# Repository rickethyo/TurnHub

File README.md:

# TurnHub

TurnHub is a local-first tabletop game-management system: turn timer, lobby,
life totals and Commander damage, player profiles and statistics. An
authoritative **Atlas** table controller runs connected games; player-facing
**Sigils**, phones and tablets and the Atlas touchscreen request the same
semantic actions from it. The Android app also runs separate standalone games;
an iPhone/iPad app is at the framework stage.

**Current firmware:** Atlas **0.7.17-dev**, Sigil **0.9.19-dev** (protocol 3).
Signed releases are published on GitHub Releases and installed from the
Android app or the Atlas portal.

Earlier Python/Raspberry Pi generations are recorded in
[Generation History](Documentation/engineering/history/GENERATION_HISTORY.md). They are
not part of this repository or the current runtime.

## Branches

`master` is the ESP32-S3/LVGL development track. The current ESP32 boards
(e-ink and OLED Sigils, the 2.8" Atlas), the test harness, the Sigil v1 PCB and
the 3D enclosures are frozen on **`legacy/gen1`**: to fix a bug on those boards,
branch from `legacy/gen1` and open the PR against it. The two never merge.

## Where to look

| Path | What |
|---|---|
| [`Atlas/`](Atlas/README.md) | ESP32 table controller: game engine, Wi-Fi AP, web portal and HTTP API, ESP-NOW radio, NVS and optional microSD storage |
| [`Sigil/`](Sigil/platformio.ini) | Touchscreen player controller: LVGL touch buttons, secure radio, pairing and speaker; one build, on the E32R28T board until the S3 Sigil |
| [`shared/simulator/`](shared/simulator/README.md) | Semi-retired desktop simulator; real Atlas/Sigil hardware is primary |
| [`Android/`](Android/README.md) | Native client: table view, player controls, guided setup and firmware updates |
| [`iOS/`](iOS/README.md) | SwiftUI iPhone/iPad foundation, core package and staged development plan; gameplay not yet implemented |
| [`protocol/`](protocol/README.md) | Client contract: JSON schemas, [`http-v1.md`](protocol/http-v1.md), example responses |
| [`shared/display/`](shared/display) | Active fonts and icons shared by Atlas, Sigil and optional simulator |
| [`shared/include/`](shared/include) | Firmware headers shared by Atlas and Sigil (radio contract, firmware package format) |
| [`Documentation/engineering/`](Documentation/engineering/README.md) | The engineering record: invariants, design references, staged work |
| [`Documentation/User Manual/`](Documentation/User%20Manual) | The user manuals: the App Manual and the Hardware Manual (newest `.docx` of each; the app bundles both) |

## Core architectural rule

**Atlas owns canonical game and table state.** Sigils, phones, the Atlas
touchscreen and simulators submit Intents and render Atlas state.
They never advance turns, resolve wins, own player identity or keep competing
game engines. See [Architectural Invariants](Documentation/engineering/ARCHITECTURAL_INVARIANTS.md).

```text
Profile (optional persistent person)
  -> Participant (one person at the current table)
    -> Controller assignment(s): physical Sigil seat, browser sessions, the app
```

Changing controllers never replaces the participant or moves its statistics.

## What works today

- Lobby with any-seated-player start (cancellable countdown), starter choice,
  turn passing with a three-second cancellable grace, pause/resume, concession,
  elimination, win claim/confirm, draw by the Atlas End match hold, rematch and reset.
- Game profiles (Generic, Magic, Commander, Yu-Gi-Oh!) with life totals,
  Commander damage and cross-player life requests the recipient approves.
- Turn timer with warning and expiry cues on Sigil lights and buzzers, the
  Atlas speaker and phones, with per-player accessibility preferences.
- Local profiles with PINs, phone-only and mixed phone/Sigil play, a Sigil
  profile picker, Admin/Game Master/Developer permissions, and table presence
  codes for protected actions.
- Deliberate pairing (60 s minimum window) over an encrypted Atlas-Sigil link,
  with forget/unpair and factory reset from menus, the portal and the BOOT button.
- Interrupted-match recovery: a power cut restores the match paused.
- Core statistics in NVS; detailed statistics, avatars and rotating
  diagnostics on an optional microSD card.
- Signed firmware updates for Atlas and both Sigil variants, delivered from
  the Android app or the portal, plus a first-run guided setup in the app.

Known limits are tracked in [Staged Changes](Documentation/engineering/STAGED_CHANGES.md).
The most important: statistics are not yet crash-safe exactly-once
([completion ordering](Documentation/engineering/STORAGE_AND_RECOVERY.md)).

## Persistence

Survives restart: profiles, PIN hashes, permissions and policy, core
statistics, seat bindings, pairings, game settings, accessibility
preferences, the Wi-Fi password, speaker volume, setup stage and touch
calibration (NVS); detailed statistics and diagnostics (microSD, optional).

RAM only: browser sessions, lobby participation and live game state, except
the interrupted-match recovery record, which restores paused and never
replays statistics.

## Building and testing

Commands for every target are in [`CLAUDE.md`](CLAUDE.md) and each
directory's README. CI (`.github/workflows/ci.yml`) runs the host suites,
contract checks, supported firmware builds and the Android tests; see
[Continuous Integration](Documentation/engineering/CONTINUOUS_INTEGRATION.md).

## Local-first

The core play path never needs a cloud service, subscription or internet
connection. Atlas serves the table on its own Wi-Fi. The broader ownership,
repairability, privacy and accessibility direction is in
[Product Principles](Documentation/PRODUCT_PRINCIPLES.md).

## Status

TurnHub is a prototype. Every Atlas and Sigil is reflashed together,
so there is no backward compatibility before release: a changed protocol or
storage layout means reflashing everything and, for storage, a factory reset.

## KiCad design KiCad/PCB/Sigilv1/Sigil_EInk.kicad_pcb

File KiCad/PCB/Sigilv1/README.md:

# Sigil Rev A electrical drafts

Rev A is drawn as two KiCad projects in this folder, plus `Sigil_JewelAdapter` (the status ring's small board, below). They share the symbol library (`Sigil.kicad_sym`) and differ only in the display interface:

| Project | Display | Display nets |
|---|---|---|
| `Sigil_EInk.kicad_pro` | Inland e-paper driver board (GxEPD2_213_B74), J2 `EPD_Module_Header` (8 pins) | EPD_SCLK, EPD_MOSI, EPD_CS, EPD_DC, EPD_RST, EPD_BUSY |
| `Sigil_OLED.kicad_pro` | Inland 1.3" OLED V2.0, J2 `OLED_Module_Header` (7 pins) | OLED_SCLK, OLED_MOSI, OLED_CS, OLED_DC, OLED_RST |

Both displays use the same sockets and GPIOs (A8/GPIO16 DC, A9/GPIO17 CS, A11/GPIO18 clock, A17/GPIO22 reset, A18/GPIO23 data); only the e-ink uses A14/GPIO21 BUSY. Both schematics also carry the buzzer interface J3 on J12/GPIO33, +3V3 from J19, and GND on A13, A19 and J6.

**Discrete LEDs and the old buttons are gone** (removed 2026-09-24). Their GPIOs are marked NC.

**Display-type strap (both, 2026-09-26).** A7/GPIO4 tells the firmware which display the board carries (`HW_TYPE_STRAP_PIN`, `Sigil/DISPLAY.md`): left NC on `Sigil_EInk` (the internal pull-up reads E-ink), tied to GND on `Sigil_OLED`. A build for the other display halts at boot, so a carrier with the wrong strap won't run.

**First-PCB footprints (2026-09-26).** Every carrier part now has a footprint and is in the BOM (through-hole except U2, SOT-23-5; U1 and the Jewel pins are local footprints in `Sigil.pretty`): J2 a 1x8 (E-ink) or 1x7 (OLED) 2.54 mm socket, J4 a JST-XH 5-pin socket for the joystick harness, J5 a JST-XH 3-pin socket for the Jewel adapter pigtail, J3 a 1x2 header for the buzzer leads, R1 an axial 0207 resistor, C2 a 10 uF ceramic on +3V3 beside the headers (5 mm disc footprint). *Planned*: footprints are chosen, no board is laid out.

**Joystick (both).** Both schematics carry J4, an unmarked 5-pin analog thumbstick that replaces the Pass/Action/Pause buttons: GND, "+5V" (fed **3.3 V**, never 5 V, since VRX/VRY swing to the supply and the ESP32 ADC is 3.3 V max), VRX to J15/GPIO34, VRY to J14/GPIO35 and SW to J13/GPIO32. VRX/VRY are ADC1 input-only pins because ADC2 is unusable under ESP-NOW. Firmware: the Sigil `sigil` and `sigil-oled` PlatformIO environments; the directions and click are the five menu keys. *Verified* on the owner's E-ink breadboard (2026-09-25): both axes read reversed as mounted, so the firmware inverts X and Y. The OLED Sigil's five pushbuttons (SW1-SW5) were replaced by the same stick on the same GPIOs on 2026-10-01 (owner); its mounting *Needs verification*.

**Status ring (both), on its own adapter board (2026-09-26).** The Adafruit NeoPixel Jewel 7 (RGBW) no longer sits on the Sigil board. `Sigil_JewelAdapter` is a small board with five pin holes where the Jewel's pads are (positions from Adafruit's [NeoJewel 7 board file](https://github.com/adafruit/Adafruit-NeoPixel-Jewel-7)): pins stand up from it and the Jewel is soldered on top, LEDs up, like it was on the breadboard. It carries C1 (470 uF bulk capacitor), the Jewel's two M2 mounting holes, an optional unfitted chain-out J3 (+5V, DOUT, GND) for more pixels after the Jewel, and J2, three holes for the bare end of a 3-wire JST-XH pigtail. The pigtail plugs into J5 on the Sigil board, a JST-XH 3-pin socket (1 +5V, 2 DIN, 3 GND, same order at both ends). On the Sigil board, GPIO26 (J10) goes through U2 and R1 (330 ohm, at the source; the Jewel has its own 470 ohm on DIN) to J5, and +5V comes from the DevKit's USB 5V (J1). Full RGBW draws about 560 mA, more than USB supplies, so the firmware caps brightness at 48/255. The ring draws the Sigil's status light from Atlas's LedState; the same information is always on a screen as text. *Verified* lit on the breadboard (owner, 2026-09-26); the adapter's pad positions are *Needs verification* (test-fit a Jewel against a 1:1 print).

**Front light output J6 (both, 2026-09-28).** A second JST-XH 3-pin socket for the possible player-facing strip on the case front lip (`STAGED_CHANGES.md`). It has its own data line rather than chaining off the Jewel adapter: the main board sits in the case base beside the front lip, while the Jewel is on the back wall. GPIO13 (socket J5; free on both boards and not a boot strap) goes through U3 (a second 74AHCT1G125, decoupled by C4) and R2 (330 ohm) to J6 pin 2; pinout as J5 (1 +5V, 2 DIN, 3 GND). J6, U3, R2 and C4 are fitted on every board (owner decision) so a strip can be added later without rework. Ring and strip share USB 5 V, so firmware must cap both (7 + 8 RGBW pixels at 48/255 is about 225 mA). No firmware drives GPIO13 yet. *Planned*.

The breadboard wiring the current firmware uses is in the [hardware reference](../../../Documentation/engineering/HARDWARE.md).

U1 is the removable, complete 38-pin ESP32 DevKit carrier interface (Inland ESP32-WROOM-32E, micro-USB, the narrow 38-pin format). Its custom symbol and local symbol library use **A1–A19 and J1–J19 as pin numbers**, not ESP32 module pad numbers. Its footprint, `Sigil.pretty/ESP32_DevKit_38_Socket_Row22.225mm` (from `build_schematic.py`), has 2.54 mm pitch and rows 22.225 mm (7/8 in) apart, and a 25.4 x 53.975 mm (1 x 2 1/8 in) outline that is not centred on the pins: the owner's breadboard fit (2026-09-28, first pins in row 1, USB end flush with the breadboard end, antenna end just reaching row 21) puts the USB end about 3.4 mm before A1/J1 and the antenna end about 4.86 mm past A19/J19. Row spacing, width, length and antenna size are the owner's ruler measurements (2026-09-28; 7/8 in rows, 1 in wide, antenna 1/4 in long from 1 7/8 in). An earlier breadboard fit suggested 22.86 mm (0.9 in), which conflicts by 0.635 mm. A 6.35 mm keep-out (no tracks, vias, pours or parts), 3/4 in wide so the pin rows stay routable, covers the WROOM-32E antenna at the A19/J19 end. It is drawn from the carrier's top side with the DevKit face up and micro-USB at the top, which mirrors the rear photo: the A row is on the left, the J row on the right, and A1/J1 at the USB end. *Needs verification*: caliper-check the row spacing and test-fit sockets before ordering. `Sigil_EInk.kicad_pcb` is routed (2026-09-28, Freerouting v2.4.1 plus a hand-placed BUZZER track, GND pours on both layers with solid pad connections); KiCad 10.0.6 CLI DRC reports 0 violations, 0 unconnected pads and 0 schematic parity issues. It is not fabrication-ready until U1 is test-fitted. The OLED PCB is still an empty placeholder.

## Authority and orientation

- GPIO functions: `Sigil/include/epaper_display.h` and the explicit SPI configuration in `Sigil/src/epaper_display.cpp` (e-ink), `Sigil/include/oled_config.h` (OLED), and `BUZZER_PIN` in `Sigil/src/main.cpp`.
- Socket identity: user-supplied [SigilBackMarked.png](reference/SigilBackMarked.png), photographed from the **BACK**, and the user's transcribed sequence. The schematics deliberately show J1 (5V) top-left and A1 (CLK) top-right in that rear-reference view.
- [The cross-check tables](CROSS_CHECK.md) are verified from both exported netlists and the firmware by `tools/verify_schematic.py`.

The rear-reference arrangement is **not** a carrier component-side footprint drawing. Future footprint work must translate the views explicitly and verify insertion against the physical part. Preserve each socket ID; do not blindly copy or mirror the schematic into a footprint.

This draft assumes power through the DevKit's own USB connector; J1/5V has no carrier connection. No additional regulator, USB-UART, BOOT, EN/reset, or other DevKit support circuitry is reproduced.

## Unresolved electrical details

- **Display J2 (both):** pin numbers follow the module's own header, pin 1 at the top, with the silkscreen labels as pin names. Order and the jumper wire color on each wire come from the owner's photos of the breadboard wiring (2026-09-24); the colors are annotations, not a harness specification. Tables are in [CROSS_CHECK.md](CROSS_CHECK.md). J2 has no footprint yet.
- **E-ink J2:** SDI, SCLK, CS, D/C, RES, BUSY, VCC, GND. The Inland driver board has two slide switches, P1 (3 / 0.47) and P2 (5VIN / 3.3VIN). J2 VCC is the DevKit 3.3 V rail (J19), so **P2 must be set to 3.3VIN** (owner decision, 2026-09-28: stay on 3.3 V; the board can take 5VIN but no supply jumper is added). The owner's working breadboard unit shows P2 on 3.3VIN and P1 on 3 (photo, 2026-09-28). Supply current and the panel itself need confirmation. The display has no carrier MISO connection.
- **OLED J2:** GND, VCC, CLK, MOSI, RES, DC, CS. The owner verified the SPI wiring, 3.3 V supply and a working image on 2026-09-24; the SH1106 controller and 128x64 geometry are inferred from the vendor example (see `Sigil/DISPLAY.md`).
- **Buzzer J3:** a logical SIG/GND interface only. Firmware proves GPIO33 tone output, but not whether the physical load is a passive piezo, magnetic transducer, or driven module. Confirm part, wiring, voltage/current, driver, bias and protection before implementing the load. No direct GPIO-drive rating is assumed.
- J3 is a plain 2-pin header (pin 1 SIG, pin 2 GND). **Locked 2026-09-28: a passive piezo**, driven directly by GPIO33 (no driver parts). A magnetic transducer was considered and rejected: louder, but it needs a transistor and flyback diode and draws 30-80 mA; a larger piezo disc is the fix if volume proves short.
- Confirm the DevKit regulator can supply the carrier/display load on +3V3 (the ring runs from USB 5 V).
- **Ring level shifter (2026-09-26):** 3.3 V data worked on the breadboard but is below the SK6812's ~3.5 V input spec, so the PCB adds U2, a 74AHCT1G125 (SOT-23-5) on +5V with C3 (100 nF): GPIO26 -> U2 -> R1 -> DIN (nets RING_DIN, RING_DIN_5V, RING_DIN_R).

## Mechanical release hold

No reliable dimensional drawing or measured dimensions were found in the repository. The photograph is sufficient for sequence and orientation, not mechanics. Measure or obtain a reliable drawing for:

- Actual pin pitch (likely 2.54 mm, not yet verified), row center spacing and pin locations.
- Exact board width/length, USB-C overhang and cable insertion envelope.
- Mounting-hole positions/diameters, if used.
- Female socket dimensions/height, insertion depth, underside and component keepouts.
- BOOT and EN/reset access plus antenna clearance requirements for the exact installed DevKit.

Use two 1x19 female socket rows so the complete DevKit remains removable. The eventual silkscreen must make A1/J1 and insertion orientation obvious. Keep USB-C accessible for flashing/debugging and leave BOOT and EN/reset operable. **No fabrication-ready DevKit footprint exists in this revision.**

## Validation and editing

KiCad 10.0.6 CLI ERC on both schematics: **0 violations**, without ERC exclusions (2026-09-24). After the 2026-09-26 changes (including the U1 rows and antenna keep-out), KiCad 10.0.6 CLI ERC on all three schematics: **0 violations**, and `verify_schematic.py` passes on KiCad-exported netlists. The files stay in the builder's compact form until KiCad re-saves them. Exported netlist checks verify all 38 socket names, the display and buzzer GPIOs against firmware, each display header pin's number, label and net, power and ground positions, that only U1/J2/J3 are present, and that every other socket is NC. Rendered schematics were visually reviewed. These checks do not resolve the electrical or mechanical holds above.

`tools/build_schematic.py` rebuilds both schematics and the symbol library deterministically. When `kicad-cli` is on PATH it then re-saves each file with `kicad-cli sch upgrade --force`, so the output matches what the KiCad editor writes (pin UUIDs are deterministic too). It overwrites both schematics and the library; do not rerun it after manual edits unless those edits have been incorporated into the script. Close the projects in KiCad first, or reload from disk afterwards, so an open copy does not overwrite the rebuild.

To validate, export each netlist and run the verifier; it refreshes CROSS_CHECK.md only after both pass:

```sh
kicad-cli sch export netlist --format kicadxml -o eink.xml Sigil_EInk.kicad_sch
kicad-cli sch export netlist --format kicadxml -o oled.xml Sigil_OLED.kicad_sch
kicad-cli sch export netlist --format kicadxml -o adapter.xml Sigil_JewelAdapter.kicad_sch
python tools/verify_schematic.py eink.xml oled.xml adapter.xml
```

Without KiCad, `python tools/offline_netlist.py Sigil_EInk.kicad_sch eink.xml` (and the same for OLED) writes an equivalent netlist from the generated files. It only understands what `build_schematic.py` writes and is not ERC.

## Planned S3 interface

These DevKit carrier/Jewel projects are preserved. Future integrated S3 LCD
boards need a separate interface design for navigation bus/INT, GPIO21 buffering
and qualified LED battery power; see [the S3 electrical plan](../../../Documentation/engineering/hardware/ESP32_S3_REFRESH.md).
No S3 fabrication-ready schematic/layout or reused footprint acceptance exists.

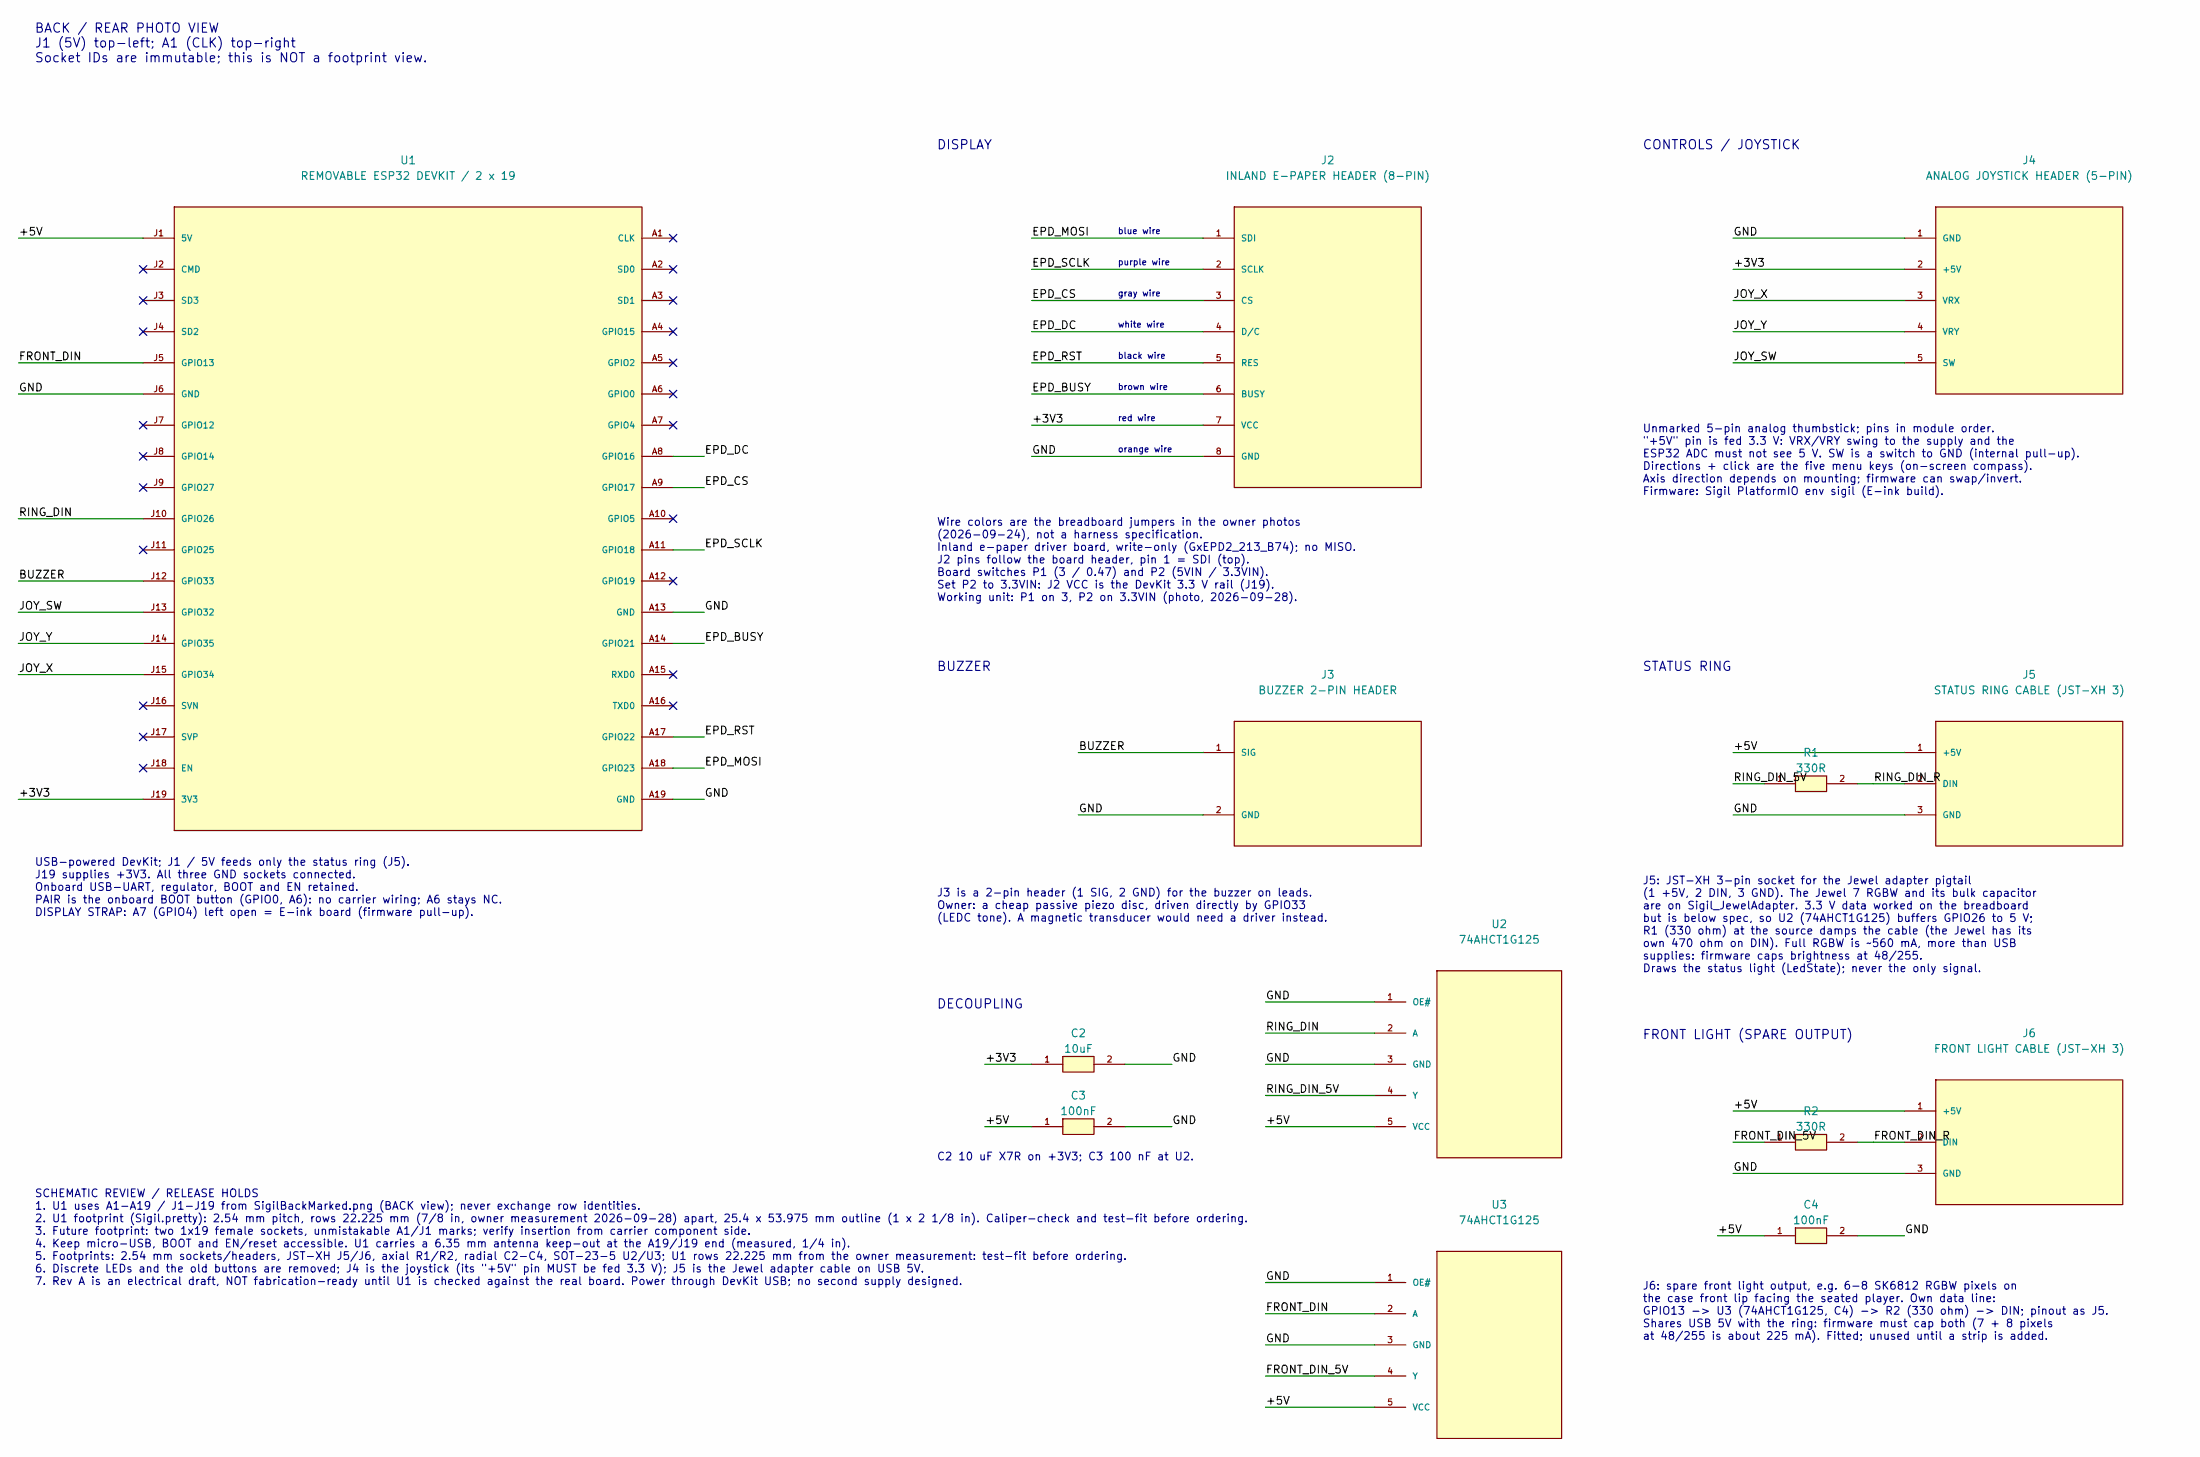
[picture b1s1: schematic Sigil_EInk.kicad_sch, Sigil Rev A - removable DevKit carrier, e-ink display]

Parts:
C2: 10uF; C_Disc_D5.0mm_W2.5mm_P5.00mm
C3, C4: 100nF; C_Disc_D5.0mm_W2.5mm_P5.00mm
J2: INLAND E-PAPER HEADER (8-PIN); JST_XH_B8B-XH-A_1x08_P2.50mm_Vertical
J3: BUZZER 2-PIN HEADER; PinHeader_1x02_P2.54mm_Vertical
J4: ANALOG JOYSTICK HEADER (5-PIN); JST_XH_B5B-XH-A_1x05_P2.50mm_Vertical
J5: STATUS RING CABLE (JST-XH 3); JST_XH_B3B-XH-A_1x03_P2.50mm_Vertical
J6: FRONT LIGHT CABLE (JST-XH 3); JST_XH_B3B-XH-A_1x03_P2.50mm_Vertical
R1, R2: 330R; R_Axial_DIN0207_L6.3mm_D2.5mm_P7.62mm_Horizontal
U1: REMOVABLE ESP32 DEVKIT / 2 x 19; ESP32_DevKit_38_Socket_Row22.225mm
U2, U3: 74AHCT1G125; SOT-23-5

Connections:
/+3V3: C2.1, J2.7 (VCC), J4.2 (+5V), U1.J19 (3V3)
/+5V: C3.1, C4.1, J5.1 (+5V), J6.1 (+5V), U1.J1 (5V), U2.5 (VCC), U3.5 (VCC)
/BUZZER: J3.1 (SIG), U1.J12 (GPIO33)
/EPD_BUSY: J2.6 (BUSY), U1.A14 (GPIO21)
/EPD_CS: J2.3 (CS), U1.A9 (GPIO17)
/EPD_DC: J2.4 (D/C), U1.A8 (GPIO16)
/EPD_MOSI: J2.1 (SDI), U1.A18 (GPIO23)
/EPD_RST: J2.5 (RES), U1.A17 (GPIO22)
/EPD_SCLK: J2.2 (SCLK), U1.A11 (GPIO18)
/FRONT_DIN: U1.J5 (GPIO13), U3.2 (A)
/FRONT_DIN_5V: R2.1, U3.4 (Y)
/FRONT_DIN_R: J6.2 (DIN), R2.2
/GND: C2.2, C3.2, C4.2, J2.8 (GND), J3.2 (GND), J4.1 (GND), J5.3 (GND), J6.3 (GND), U1.A13 (GND), U1.A19 (GND), U1.J6 (GND), U2.1 (OE#), U2.3 (GND), U3.1 (OE#), U3.3 (GND)
/JOY_SW: J4.5 (SW), U1.J13 (GPIO32)
/JOY_X: J4.3 (VRX), U1.J15 (GPIO34)
/JOY_Y: J4.4 (VRY), U1.J14 (GPIO35)
/RING_DIN: U1.J10 (GPIO26), U2.2 (A)
/RING_DIN_5V: R1.1, U2.4 (Y)
/RING_DIN_R: J5.2 (DIN), R1.2

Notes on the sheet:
C2 10 uF X7R on +3V3; C3 100 nF at U2.
CONTROLS / JOYSTICK
USB-powered DevKit; J1 / 5V feeds only the status ring (J5). J19 supplies +3V3. All three GND sockets connected. Onboard USB-UART, regulator, BOOT and EN retained. PAIR is the onboard BOOT button (GPIO0, A6): no carrier wiring; A6 stays NC. DISPLAY STRAP: A7 (GPIO4) left open = E-ink board (firmwar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
purple wire
BACK / REAR PHOTO VIEW J1 (5V) top-left; A1 (CLK) top-right Socket IDs are immutable; this is NOT a footprint view.
gray wire
DECOUPLING
orange wire
brown wire
Wire colors are the breadboard jumpers in the owner photos (2026-09-24), not a harness specification. Inland e-paper driver board, write-only (GxEPD2_213_B74); no MISO. J2 pins follow the board header, pin 1 = SDI (top). Board switches P1 (3 / 0.47) and P2 (5VIN / 3.3VIN). Set P2 to 3.3VIN: J2 VCC 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
blue wire
DISPLAY
red wire
FRONT LIGHT (SPARE OUTPUT)
J6: spare front light output, e.g. 6-8 SK6812 RGBW pixels on the case front lip facing the seated player. Own data line: GPIO13 -> U3 (74AHCT1G125, C4) -> R2 (330 ohm) -> DIN; pinout as J5. Shares USB 5V with the ring: firmware must cap both (7 + 8 pixels at 48/255 is about 225 mA). Fitted; unused 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
J5: JST-XH 3-pin socket for the Jewel adapter pigtail (1 +5V, 2 DIN, 3 GND). The Jewel 7 RGBW and its bulk capacitor are on Sigil_JewelAdapter. 3.3 V data worked on the breadboard but is below spec, so U2 (74AHCT1G125) buffers GPIO26 to 5 V; R1 (330 ohm) at the source damps the cable (the Jewel has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
STATUS RING
SCHEMATIC REVIEW / RELEASE HOLDS 1. U1 uses A1-A19 / J1-J19 from SigilBackMarked.png (BACK view); never exchange row identities. 2. U1 footprint (Sigil.pretty): 2.54 mm pitch, rows 22.225 mm (7/8 in, owner measurement 2026-09-28) apart, 25.4 x 53.975 mm outline (1 x 2 1/8 in). Caliper-check and tes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
black wire
white wire
Unmarked 5-pin analog thumbstick; pins in module order. "+5V" pin is fed 3.3 V: VRX/VRY swing to the supply and the ESP32 ADC must not see 5 V. SW is a switch to GND (internal pull-up). Directions + click are the five menu keys (on-screen compass). Axis direction depends on mounting; firmware can s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
J3 is a 2-pin header (1 SIG, 2 GND) for the buzzer on leads. Owner: a cheap passive piezo disc, driven directly by GPIO33 (LEDC tone). A magnetic transducer would need a driver instead.
BUZZER

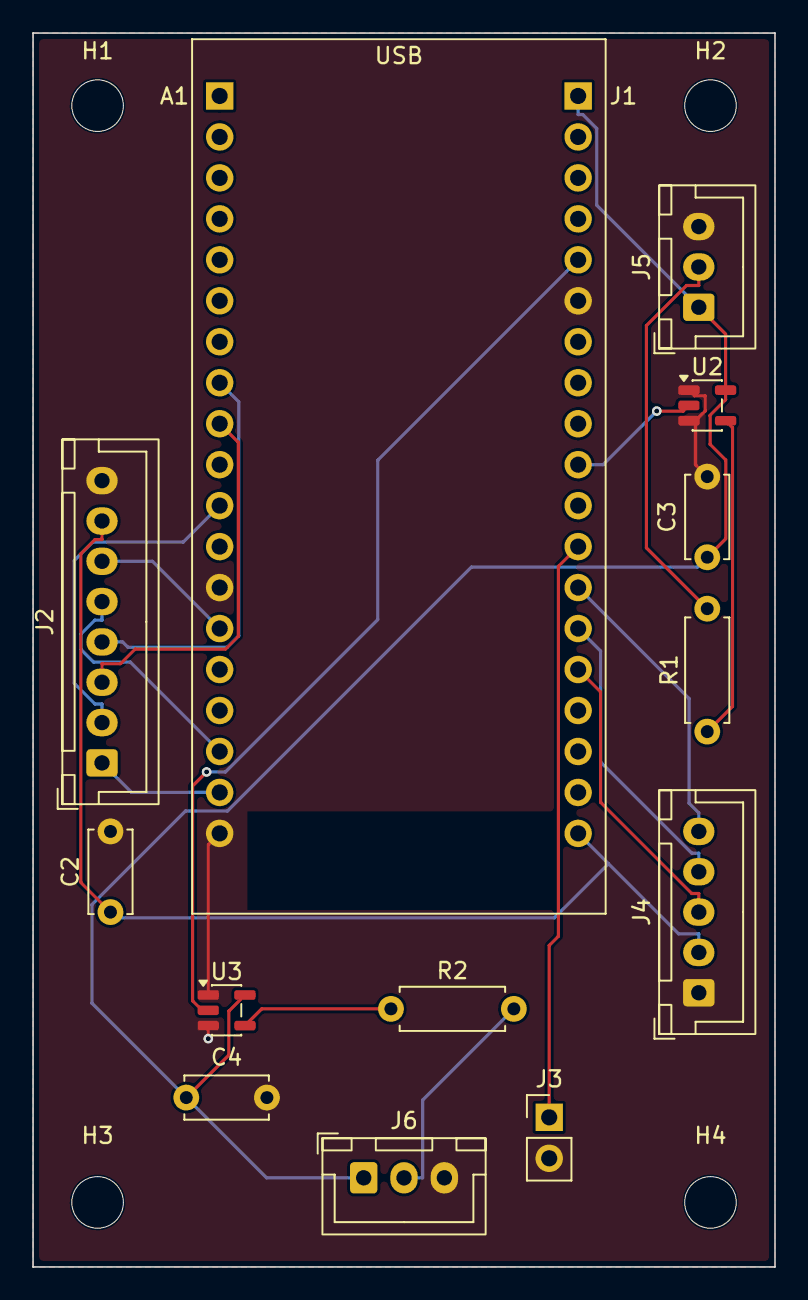
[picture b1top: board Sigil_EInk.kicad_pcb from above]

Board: 2 copper layers, 46.0 x 76.5 mm, 17 parts (0 on the bottom side), 19 nets.

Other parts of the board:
H1, H2, H3, H4: M3; MountingHole_3.2mm_M3

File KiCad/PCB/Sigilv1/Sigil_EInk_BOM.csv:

"Refs","Value","Footprint","Qty","DNP"
"C2","10uF","Capacitor_THT:C_Disc_D5.0mm_W2.5mm_P5.00mm","1",""
"C3,C4","100nF","Capacitor_THT:C_Disc_D5.0mm_W2.5mm_P5.00mm","2",""
"J2","INLAND E-PAPER HEADER (8-PIN)","Connector_JST:JST_XH_B8B-XH-A_1x08_P2.50mm_Vertical","1",""
"J3","BUZZER 2-PIN HEADER","Connector_PinHeader_2.54mm:PinHeader_1x02_P2.54mm_Vertical","1",""
"J4","ANALOG JOYSTICK HEADER (5-PIN)","Connector_JST:JST_XH_B5B-XH-A_1x05_P2.50mm_Vertical","1",""
"J5","STATUS RING CABLE (JST-XH 3)","Connector_JST:JST_XH_B3B-XH-A_1x03_P2.50mm_Vertical","1",""
"J6","FRONT LIGHT CABLE (JST-XH 3)","Connector_JST:JST_XH_B3B-XH-A_1x03_P2.50mm_Vertical","1",""
"R1,R2","330R","Resistor_THT:R_Axial_DIN0207_L6.3mm_D2.5mm_P7.62mm_Horizontal","2",""
"U1","REMOVABLE ESP32 DEVKIT / 2 x 19","Sigil:ESP32_DevKit_38_Socket_Row22.225mm","1",""
"U2,U3","74AHCT1G125","Package_TO_SOT_SMD:SOT-23-5","2",""

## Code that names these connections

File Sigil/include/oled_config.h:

#pragma once

#include <stdint.h>

namespace TurnHubSigil {

enum class OledController { Unspecified, Sh1106 };
enum class OledBus { Unspecified, I2c, SoftwareSpi };
enum class OledPower { Unspecified, InternalChargePump };

// Field defaults are unset so a partially filled config is rejected before any
// bus/pin initialization. OLED_CONFIG below is the selected hardware profile.
struct OledConfig {
  OledController controller = OledController::Unspecified;
  OledBus bus = OledBus::Unspecified;
  uint16_t width = 0;   // Native pixels (adapter supports 128x64).
  uint16_t height = 0;
  int8_t rotation = -1; // 0 or 2; portrait layout is not scaffolded.
  OledPower power = OledPower::Unspecified;
  int8_t reset = -2;    // GPIO, or explicitly -1 for no reset connection.
  int16_t i2cAddress = -1; // Explicit 7-bit address, never auto-selected.
  uint32_t i2cClockHz = 0;
  int8_t sda = -1;        // I2C GPIO assignments.
  int8_t scl = -1;
  int8_t mosi = -1;       // 4-wire software SPI GPIO assignments.
  int8_t sclk = -1;
  int8_t dc = -1;
  int8_t cs = -1;
};

// Inland 1.3-inch OLED V2.0 on the Sigil carrier's EPD header, 4-wire SPI.
// Owner-verified wiring (2026-09-24) against the Sigil schematic:
//   CLK A11/GPIO18, MOSI A18/GPIO23, RES A17/GPIO22, DC A8/GPIO16,
//   CS A9/GPIO17, VCC 3.3 V, GND common. EPD_BUSY/GPIO21 is unused.
// Controller SH1106 128x64 is inferred from the vendor (KS0056) example and
// still needs confirmation on the panel itself.
inline OledConfig makeOledConfig() {
  OledConfig c{};
  c.controller = OledController::Sh1106;
  c.bus = OledBus::SoftwareSpi;
  c.width = 128;
  c.height = 64;
  c.rotation = 2;  // Flipped 180 after the 2026-09-30 rewiring.
  c.power = OledPower::InternalChargePump;
  c.reset = 22;
  c.mosi = 23;
  c.sclk = 18;
  c.dc = 16;
  c.cs = 17;
  return c;
}

const OledConfig OLED_CONFIG = makeOledConfig();

}  // namespace TurnHubSigil
